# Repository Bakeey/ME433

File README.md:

# ME433
Repo of Klemens Iten for MECH_ENG 433: Advanced Mechatronics, Spring 2023 @ Northwestern University.

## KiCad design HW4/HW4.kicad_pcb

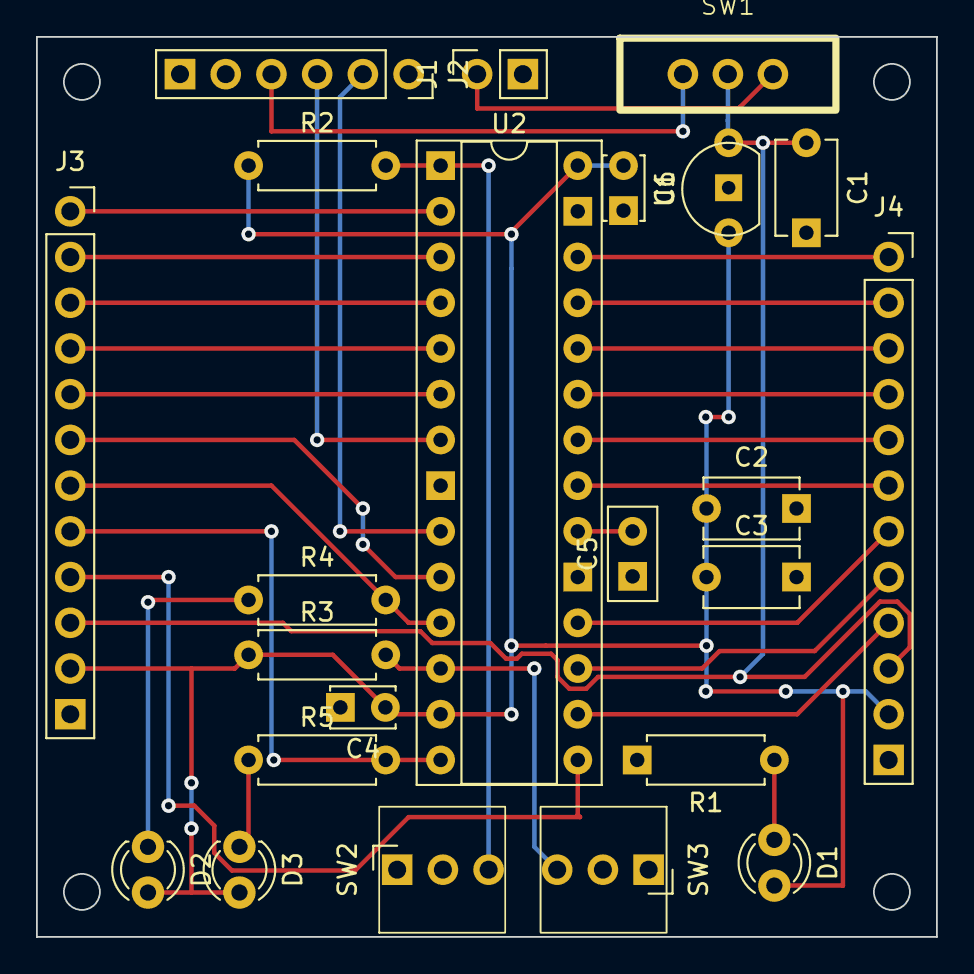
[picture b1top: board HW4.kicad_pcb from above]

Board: 2 copper layers, 50.0 x 50.0 mm, 23 parts (0 on the bottom side), 31 nets.

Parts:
C1, C2, C3: 1uF; C_Disc_D5.1mm_W3.2mm_P5.00mm
C4, C6: 0.1uF; C_Disc_D3.4mm_W2.1mm_P2.50mm
C5: 10uF; C_Disc_D5.0mm_W2.5mm_P2.50mm
D1: RED; LED_D3.0mm
D2: GREEN; LED_D3.0mm
D3: YELLOW; LED_D3.0mm
J1: 6V Battery; PinSocket_1x02_P2.54mm_Vertical
J2: CP2102N; PinSocket_1x06_P2.54mm_Vertical
J3: Left GPIO; PinSocket_1x12_P2.54mm_Vertical
J4: Right GPIO; PinSocket_1x12_P2.54mm_Vertical
R1, R4, R5: 330R; R_Axial_DIN0207_L6.3mm_D2.5mm_P7.62mm_Horizontal
R2, R3: 10kR; R_Axial_DIN0207_L6.3mm_D2.5mm_P7.62mm_Horizontal
SW1: SW_SPDT; Switch_3W
SW2: RESET; Pushbutton
SW3: USER; Pushbutton
U1: AP7381-3.3V; TO-92L_Inline
U2: PIC32MX170F256B; DIP-28_W7.62mm_Socket

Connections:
+3.3V: C2.1, C3.1, C4.1, C6.1, D1.2 (A), D2.2 (A), D3.2 (A), J3.11, J4.11, R2.1, R3.1, U1.1 (V_{I}), U2.13 (V_{DD}), U2.28 (AV_{DD})
+5V: J2.4, SW1.1 (A)
/A0: J3.1, U2.2 (A0)
/A1: J3.2, U2.3 (A1)
/A3: J3.6, U2.10 (A3)
/B0: J3.3, U2.4 (B0)
/B1: J3.4, U2.5 (B1)
/B2: J3.5, U2.6 (B2)
/B6: J3.9, U2.15 (B6)
/B7: J4.9, U2.16 (B7)
/B8: J4.8, U2.17 (B8)
/B9: J4.7, U2.18 (B9)
/B10: J4.6, U2.21 (B10)
/B11: J4.5, U2.22 (B11)
/B12: J4.4, U2.23 (B12)
/B13: J4.3, U2.24 (B13)
/B14: J4.2, U2.25 (B14)
/B15: J4.1, U2.26 (B15)
/GRN: J3.7, R4.2, U2.11 (B4)
/MCLR: R2.2, SW2.3, U2.1 (~MCLR)
/RX: J2.2, U2.9 (A2)
/TX: J2.3, U2.7 (B3)
/USR: R3.2, SW3.3, U2.12 (A4)
/V_{IN}: C1.1, J3.10, J4.10, SW1.2 (B), U1.3 (GND)
/YLLW: J3.8, R5.2, U2.14 (B5)
GND: C1.2, C2.2, C3.2, C4.2, C5.1, C6.2, J1.2, J2.6, J3.12, J4.12, R1.2, SW2.1, SW3.1, U1.2 (V_{O}), U2.8 (V_{SS}), U2.19 (V_{SS}), U2.27 (AV_{SS})
unnamed: D1.1 (K), R1.1
unnamed: D2.1 (K), R4.1
unnamed: D3.1 (K), R5.1
unnamed: J1.1, SW1.3 (C)
unnamed: C5.2, U2.20 (V_{CAP})

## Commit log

2023-04-01 HW2 started
2023-04-02 reverted main loop changes
2023-04-03 continuous blining for testing
2023-04-03 started DEV branch
2023-04-03 git repo cleanup
2023-04-03 finished HW2 code
2023-04-03 added deliverables
2023-04-03 updated code deliverable
2023-04-03 added circuit diagram
2023-04-03 edited circuit diagram (missing user button lol)
2023-04-05 finished HW3
2023-04-07 HW4 schematic done
2023-04-14 added files HW5
2023-04-14 HW5 defined SPI I/O pins
2023-04-15 HW5 done
2023-04-21 HW6 done, I guess
2023-04-21 HW6 done
2023-04-28 HW7 done
2023-04-28 HW7 added deliverables
2023-04-29 HW8 added files
2023-04-29 HW8 done
2023-05-04 HW10 started
2023-05-04 HW10 further
2023-05-04 HW10 solid color changing
2023-05-04 HW10 done
2023-05-04 HW10 adjustment to header files
2023-05-08 HW9 done
2023-05-11 HW11 started
2023-05-11 HW4 DONE
2023-05-11 HW11 added deliverables
2023-05-30 HW4 added readme for pictures
2023-05-31 HW13 done
2023-06-01 HW14 done
2023-06-08 HW12 done
2023-06-08 HW16 DONE
2023-06-08 HW15 late but done
2023-06-08 HW15 Update readme.md
